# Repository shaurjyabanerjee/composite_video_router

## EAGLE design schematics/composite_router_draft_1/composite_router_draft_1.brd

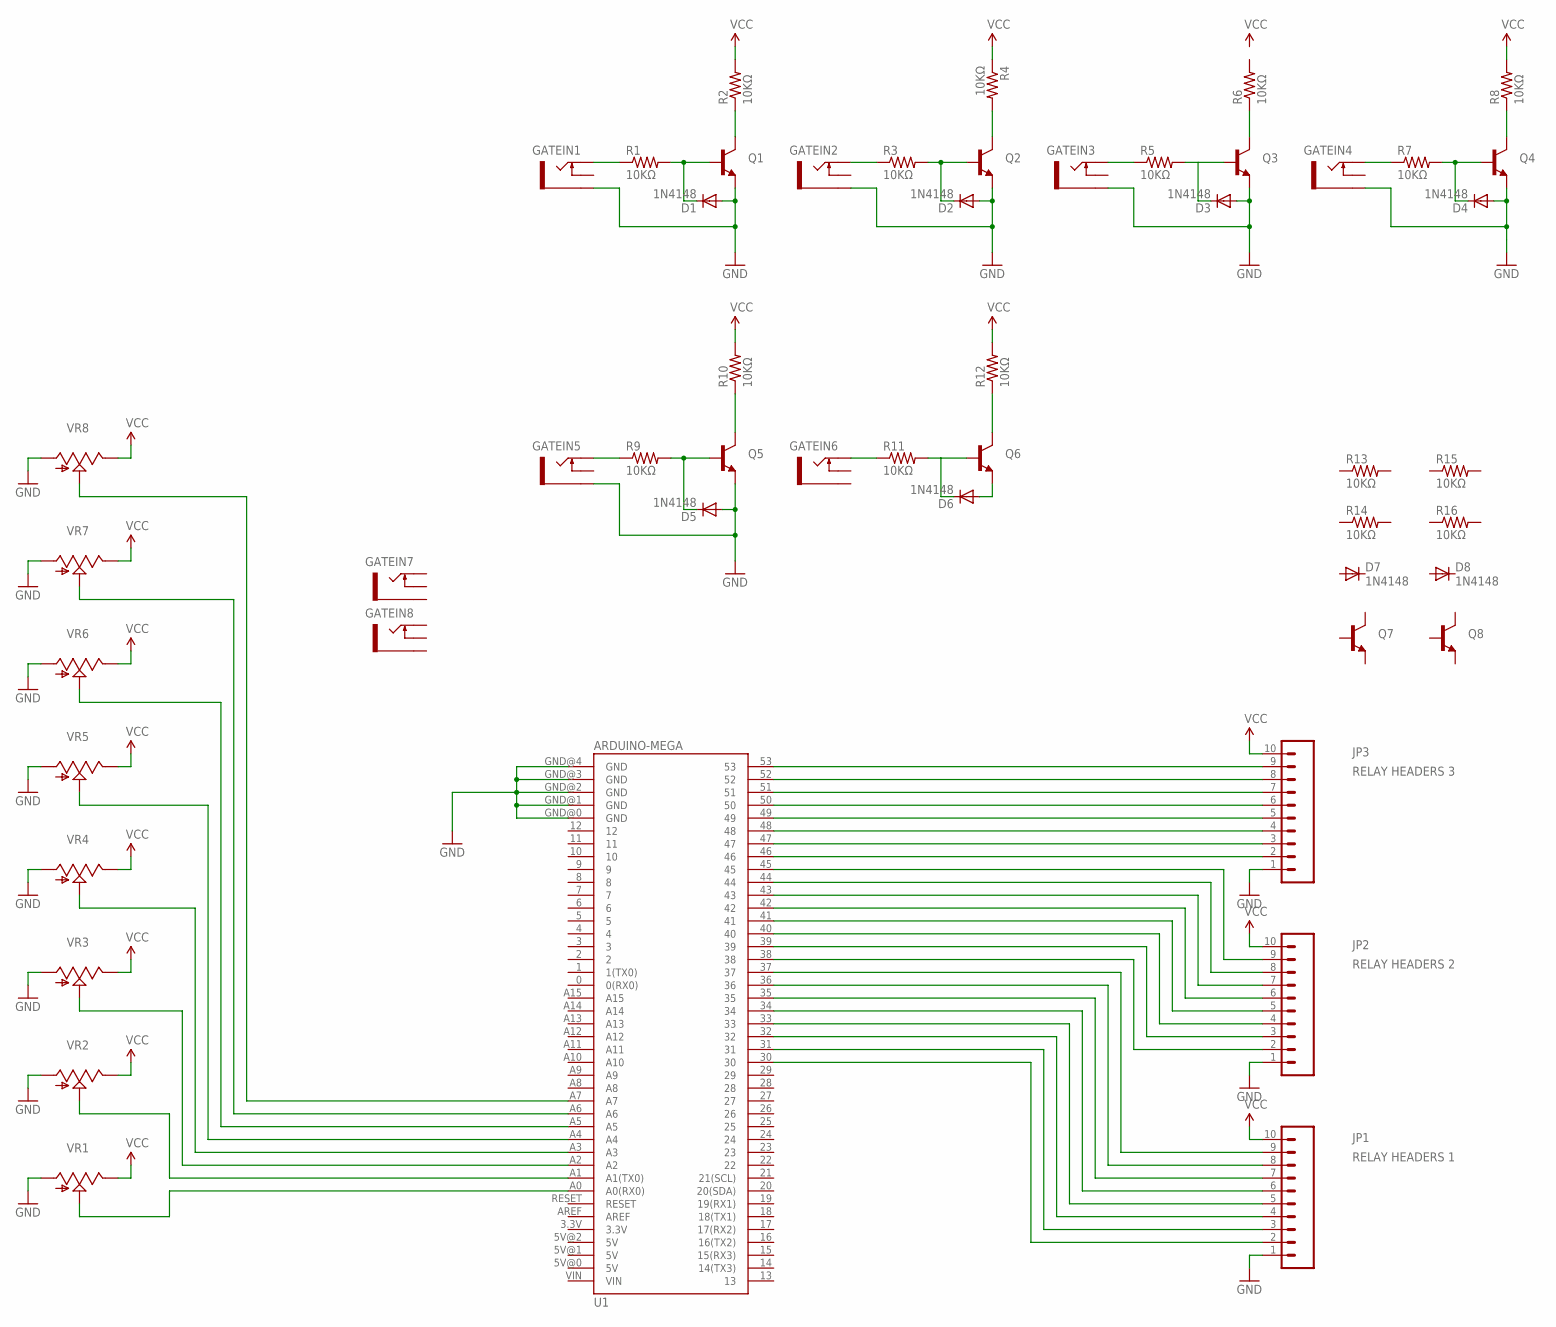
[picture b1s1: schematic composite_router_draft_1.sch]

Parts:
D1, D2, D3, D4, D5, D6, D7, D8: 1N4148; DO35-7
GATEIN1, GATEIN2, GATEIN3, GATEIN4, GATEIN5, GATEIN6, GATEIN7, GATEIN8: THONKICONNNEW; WQP-PJ301M-12_JACK
JP1: RELAY HEADERS 1; 1X10
JP2: RELAY HEADERS 2; 1X10
JP3: RELAY HEADERS 3; 1X10
Q1, Q2, Q3, Q4, Q5, Q6, Q7, Q8: TRANSISTOR_NPN2N3904; TO-92
R1, R2, R3, R4, R5, R6, R7, R8, R9, R10, R11, R12, R13, R14, R15, R16: 10KΩ; AXIAL-0.4
U1: ARDUINO-MEGA; ARDUINO_MEGA
VR1, VR2, VR3, VR4, VR5, VR6, VR7, VR8: 9MM_SNAP-IN_POT_; 9MM_SNAP-IN_POT

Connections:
GND: D1.A, D2.A, D3.A, D4.A, D5.A, GATEIN1.P$3_SLEEVE (SLEEVE), GATEIN2.P$3_SLEEVE (SLEEVE), GATEIN3.P$3_SLEEVE (SLEEVE), GATEIN4.P$3_SLEEVE (SLEEVE), GATEIN5.P$3_SLEEVE (SLEEVE), JP1.1, JP2.1, JP3.1, Q1.1 (E), Q2.1 (E), Q3.1 (E), Q4.1 (E), Q5.1 (E), U1.GND@0 (GND), U1.GND@1 (GND), U1.GND@2 (GND), U1.GND@3 (GND), U1.GND@4 (GND), VR1.1 (A), VR2.1 (A), VR3.1 (A), VR4.1 (A), VR5.1 (A), VR6.1 (A), VR7.1 (A), VR8.1 (A)
unnamed: JP3.9, U1.53
unnamed: JP3.8, U1.52
unnamed: JP3.7, U1.51
unnamed: JP3.6, U1.50
unnamed: JP3.5, U1.49
unnamed: JP3.4, U1.48
unnamed: JP3.3, U1.47
unnamed: JP3.2, U1.46
unnamed: JP2.9, U1.45
unnamed: JP2.8, U1.44
unnamed: JP2.7, U1.43
unnamed: JP2.6, U1.42
unnamed: JP2.5, U1.41
unnamed: JP2.4, U1.40
unnamed: JP2.3, U1.39
unnamed: JP2.2, U1.38
unnamed: JP1.9, U1.37
unnamed: JP1.8, U1.36
unnamed: JP1.7, U1.35
unnamed: JP1.6, U1.34
unnamed: JP1.5, U1.33
unnamed: JP1.4, U1.32
unnamed: JP1.3, U1.31
unnamed: JP1.2, U1.30
unnamed: GATEIN1.P$1_TIP (TIP), R1.P$1 (1)
unnamed: U1.A0 (A0(RX0)), VR1.2 (S)
unnamed: U1.A1 (A1(TX0)), VR2.2 (S)
unnamed: U1.A2, VR3.2 (S)
unnamed: U1.A3, VR4.2 (S)
unnamed: U1.A4, VR5.2 (S)
unnamed: U1.A5, VR6.2 (S)
unnamed: U1.A6, VR7.2 (S)
unnamed: U1.A7, VR8.2 (S)
unnamed: D1.C, Q1.2 (B), R1.P$2 (2)
unnamed: GATEIN3.P$1_TIP (TIP), R5.P$1 (1)
unnamed: D3.C, Q3.2 (B), R5.P$2 (2)
unnamed: Q1.3 (C), R2.P$1 (1)
unnamed: D2.C, Q2.2 (B), R3.P$2 (2)
unnamed: Q2.3 (C), R4.P$2 (2)
unnamed: GATEIN2.P$1_TIP (TIP), R3.P$1 (1)
unnamed: Q3.3 (C), R6.P$1 (1)
unnamed: GATEIN4.P$1_TIP (TIP), R7.P$1 (1)
unnamed: D4.C, Q4.2 (B), R7.P$2 (2)
unnamed: Q4.3 (C), R8.P$1 (1)
unnamed: GATEIN5.P$1_TIP (TIP), R9.P$1 (1)
unnamed: D5.C, Q5.2 (B), R9.P$2 (2)
unnamed: Q5.3 (C), R10.P$1 (1)
unnamed: GATEIN6.P$1_TIP (TIP), R11.P$1 (1)
unnamed: D6.C, Q6.2 (B), R11.P$2 (2)
unnamed: Q6.3 (C), R12.P$1 (1)
unnamed: D6.A, Q6.1 (E)
VCC: JP1.10, JP2.10, JP3.10, R2.P$2 (2), R4.P$1 (1), R8.P$2 (2), R10.P$2 (2), R12.P$2 (2), VR1.3 (E), VR2.3 (E), VR3.3 (E), VR4.3 (E), VR5.3 (E), VR6.3 (E), VR7.3 (E), VR8.3 (E)

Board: 2 copper layers, 52 parts (0 on the bottom side), 53 nets, no tracks yet.

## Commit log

2016-11-02 created folder structure - first commit
2016-11-03 started making schematic first draft
2016-11-03 tested arduino relay

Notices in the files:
parts and their libraries:
SparkFun-Connectors: Licensing: Creative Commons ShareAlike 4.0 International - https://creativecommons.org/licenses/by-sa/4.0
